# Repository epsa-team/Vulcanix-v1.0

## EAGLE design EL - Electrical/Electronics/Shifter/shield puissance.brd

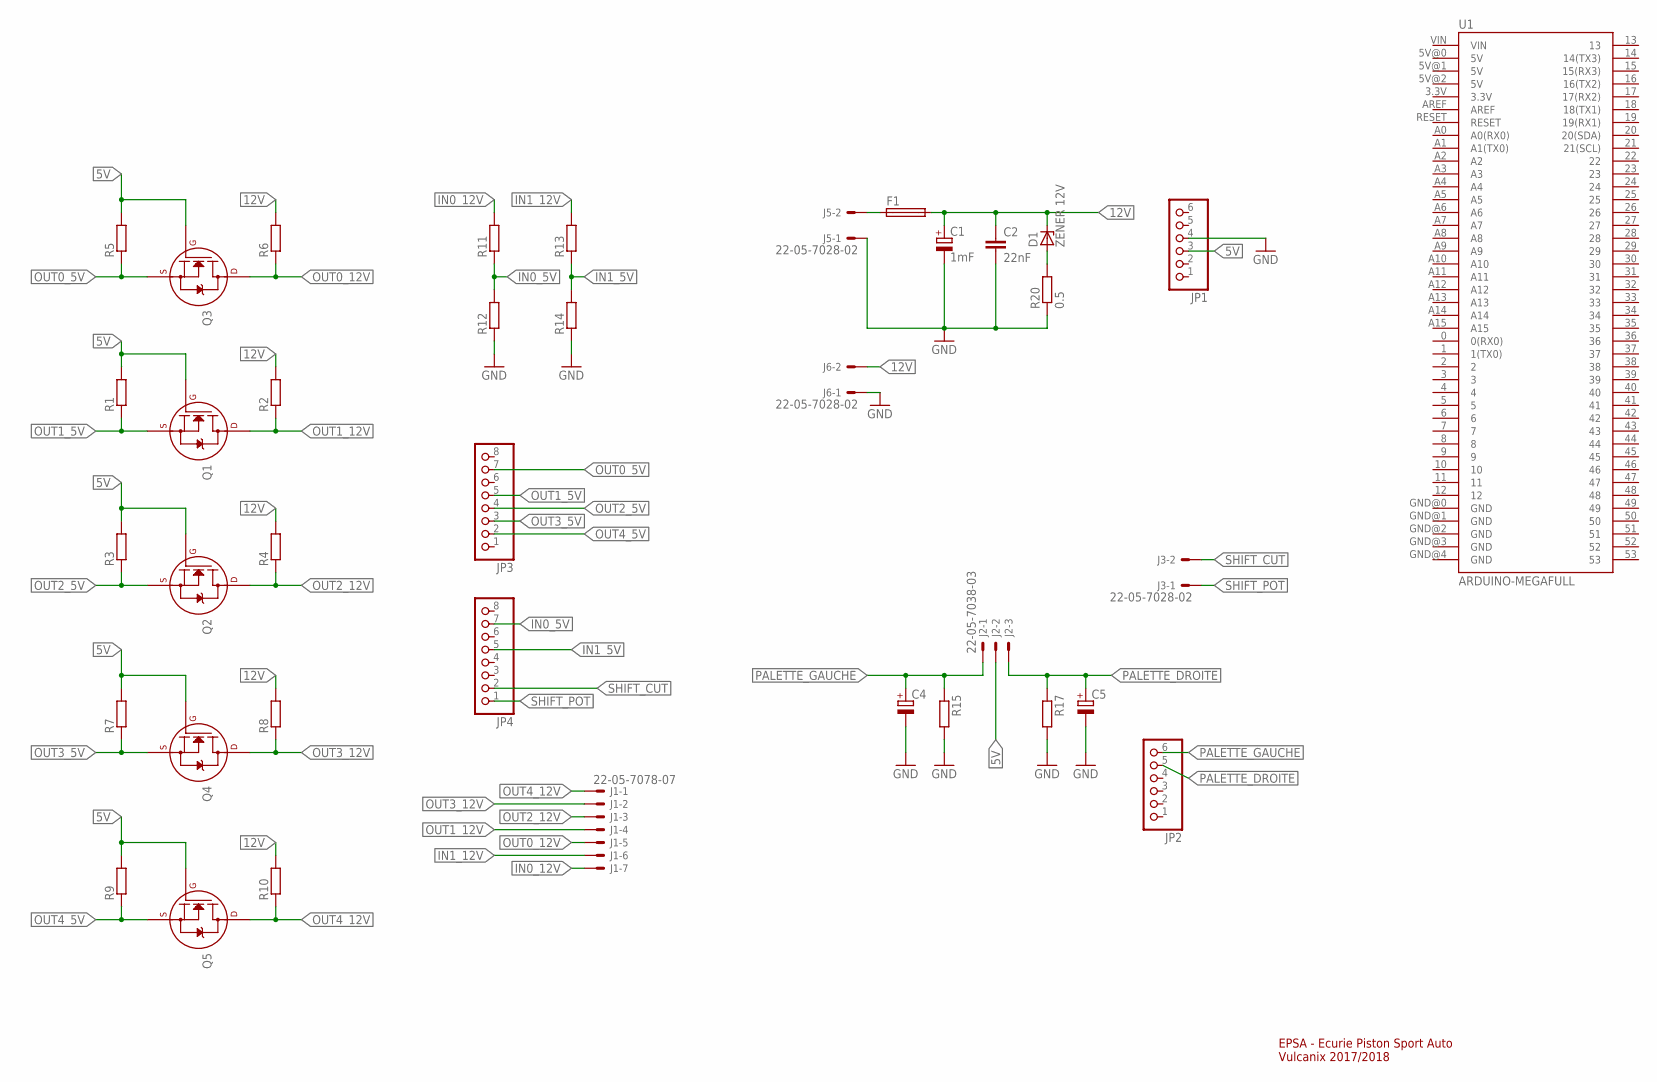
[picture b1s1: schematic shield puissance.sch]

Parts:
C1: 1mF; E2,5-6E
C2: 22nF; C025-025X050
C4, C5: CPOL-EUE2,5-6E; E2,5-6E
D1: ZENER 12V; DO41Z10
F1: SH25
J1: 22-05-7078-07; 7395-07
J2: 22-05-7038-03; 7395-03
J3, J5, J6: 22-05-7028-02; 7395-02
JP1, JP2: HEADER-1X6; 1X06_OVAL
JP3, JP4: HEADER-1X8; 1X08_OVAL
Q1, Q2, Q3, Q4, Q5: 2N7000_TO92; TO-92
R1, R2, R3, R4, R5, R6, R7, R8, R9, R10, R11, R12, R13, R14, R15, R17: R-EU_0204/7; 0204/7
R20: 0.5; 0309/12
U1: ARDUINO-MEGAFULL; ARDUINO_MEGA

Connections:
5V: J2.2, JP1.3, Q1.2 (G), Q2.2 (G), Q3.2 (G), Q4.2 (G), Q5.2 (G), R1.2, R3.2, R5.2, R7.2, R9.2
12V: C1.+, C2.1, D1.C, F1.2, J6.2, R2.2, R4.2, R6.2, R8.2, R10.2
GND: C1.-, C2.2, C4.-, C5.-, J5.1, J6.1, JP1.4, R12.1, R14.1, R15.2, R17.2, R20.1
IN0_5V: JP4.7, R11.1, R12.2
IN0_12V: J1.7, R11.2
IN1_5V: JP4.5, R13.1, R14.2
IN1_12V: J1.6, R13.2
unnamed: F1.1, J5.2
unnamed: D1.A, R20.2
OUT0_5V: JP3.7, Q3.1 (S), R5.1
OUT0_12V: J1.5, Q3.3 (D), R6.1
OUT1_5V: JP3.5, Q1.1 (S), R1.1
OUT1_12V: J1.4, Q1.3 (D), R2.1
OUT2_5V: JP3.4, Q2.1 (S), R3.1
OUT2_12V: J1.3, Q2.3 (D), R4.1
OUT3_5V: JP3.3, Q4.1 (S), R7.1
OUT3_12V: J1.2, Q4.3 (D), R8.1
OUT4_5V: JP3.2, Q5.1 (S), R9.1
OUT4_12V: J1.1, Q5.3 (D), R10.1
PALETTE_DROITE: C5.+, J2.3, JP2.5, R17.1
PALETTE_GAUCHE: C4.+, J2.1, JP2.6, R15.1
SHIFT_CUT: J3.2, JP4.2
SHIFT_POT: J3.1, JP4.1

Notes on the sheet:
EPSA - Ecurie Piston Sport Auto Vulcanix 2017/2018

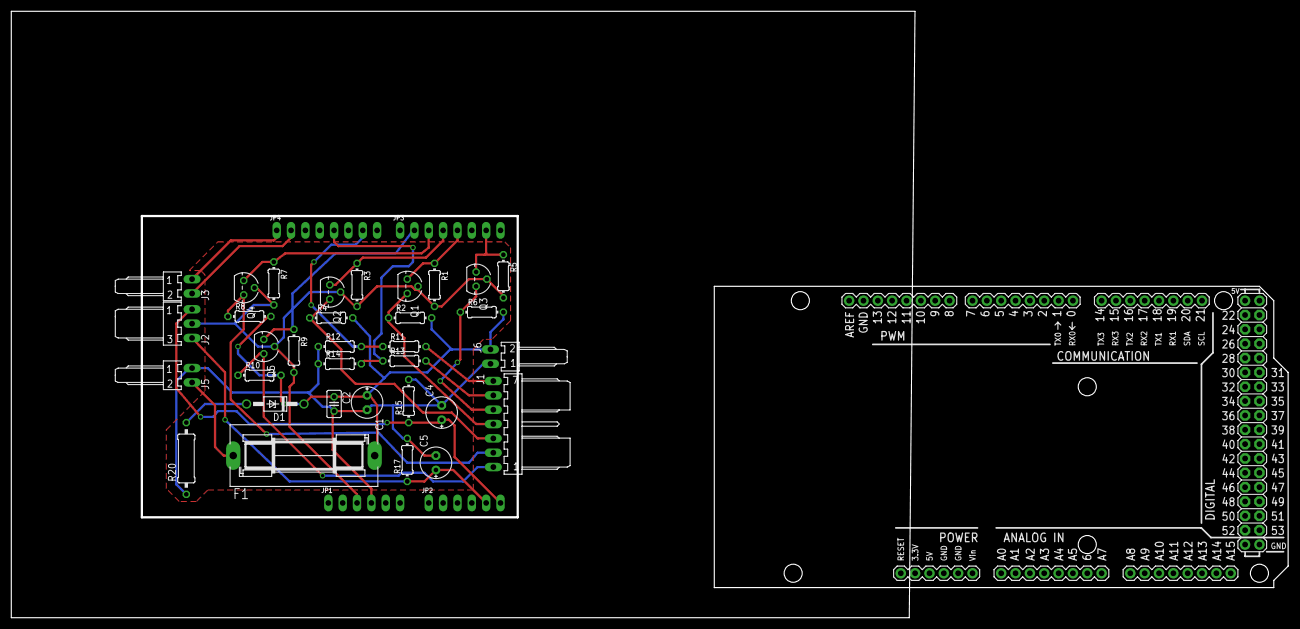
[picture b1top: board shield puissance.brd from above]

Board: 2 copper layers, 226.1 x 107.4 mm, 38 parts (0 on the bottom side), 23 nets.

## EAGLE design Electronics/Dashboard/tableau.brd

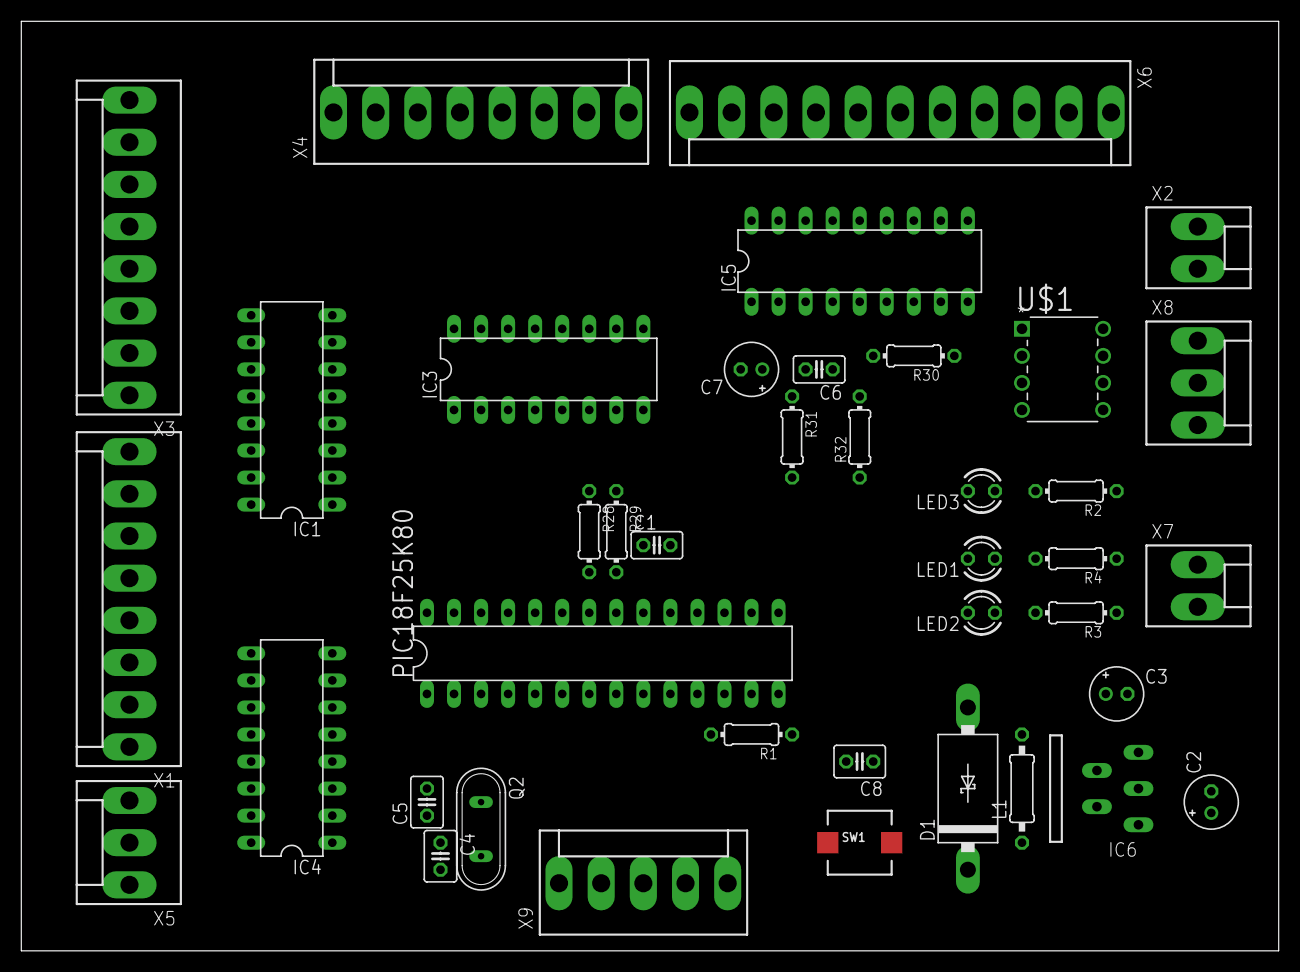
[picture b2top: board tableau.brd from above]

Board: 2 copper layers, 118.1 x 87.3 mm, 40 parts (0 on the bottom side), 69 nets, no tracks yet.

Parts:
C1: 0.1uF,20V; C025-025X050
C2, C3: 100uF; E2-5
C4, C5, C8: C025-030X050
C6: C025-025X050
C7: 10uF; E2-5
D1: 1N5822; DO201T15
IC1, IC3, IC4: 74LS47N; DIL16
IC5: LM3914N; DIL18
IC6: LM2576T; TO220-5
L1: 100uH; 0207/10
LED1, LED2, LED3: VERT; LED3MM
PIC18F25K80: PIC18F2580-I/SP; DIL28-3
Q2: QS
R1, R2, R3, R4, R28, R29, R30: 0204/7
R31: 3.83k; 0204/7
R32: 1.21k; 0204/7
SW1: PUSHBUTTON_SMD_SJ
U$1: MCP2551-I/P; DIP254P762X432-8
X1, X3, X4: KK-156-8
X2, X7: KK-156-2
X5, X8: KK-156-3
X6: KK-156-11
X9: KK-156-5

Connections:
CAN_H: U$1.6, X8.1
CAN_L: U$1.7, X8.3
CAN_RX: PIC18F25K80.24, U$1.4
CAN_TX: PIC18F25K80.23, U$1.1
D0EAU_0: IC4.7, PIC18F25K80.15
D0EAU_1: IC4.1, PIC18F25K80.16
D0EAU_2: IC4.2, PIC18F25K80.25
D0EAU_3: IC4.6, PIC18F25K80.26
D1EAU_0: IC1.7, PIC18F25K80.12
D1EAU_1: IC1.1, PIC18F25K80.11
D1EAU_2: IC1.2, PIC18F25K80.7
D1EAU_3: IC1.6, PIC18F25K80.6
D2EAU: PIC18F25K80.14, X5.1, X5.2
DRAP_0: IC3.7, PIC18F25K80.4
DRAP_1: IC3.1, PIC18F25K80.3
DRAP_2: IC3.2, PIC18F25K80.2
GND: C1.2, C2.-, C3.-, C4.1, C5.1, C6.2, C7.-, C8.1, D1.A, IC1.8, IC3.6, IC3.8, IC4.8, IC5.2, IC5.4, IC6.3, IC6.5, LED1.K, LED2.K, LED3.K, PIC18F25K80.8, PIC18F25K80.19, R28.1, R29.1, R31.1, SW1.P$1, U$1.2, U$1.8, X7.2, X8.2, X9.3
HOMING: PIC18F25K80.22, R28.2
MCLR: C8.2, PIC18F25K80.1, R1.1, SW1.P$2, X9.5
unnamed: LED1.A, R4.2
unnamed: IC4.13, X1.1
unnamed: LED2.A, R3.2
unnamed: IC4.12, X1.2
unnamed: IC4.11, X1.3
unnamed: IC4.10, X1.4
unnamed: IC4.9, X1.5
unnamed: IC4.15, X1.6
unnamed: IC4.14, X1.7
unnamed: IC1.13, X3.1
unnamed: IC1.12, X3.2
unnamed: IC1.11, X3.3
unnamed: IC1.10, X3.4
unnamed: IC1.9, X3.5
unnamed: IC1.15, X3.6
unnamed: IC1.14, X3.7
unnamed: IC3.13, X4.1
unnamed: IC3.12, X4.2
unnamed: IC3.11, X4.3
unnamed: C2.+, IC6.1
unnamed: IC3.10, X4.4
unnamed: IC3.9, X4.5
unnamed: IC3.15, X4.6
unnamed: IC3.14, X4.7
unnamed: IC5.10, X6.1
unnamed: IC5.11, X6.2
unnamed: IC5.12, X6.3
unnamed: IC5.13, X6.4
unnamed: IC5.14, X6.5
unnamed: IC5.15, X6.6
unnamed: IC5.16, X6.7
unnamed: IC5.17, X6.8
unnamed: IC5.18, X6.9
unnamed: IC5.1, X6.10
unnamed: LED3.A, R2.2
unnamed: C6.1, IC5.5, R30.2
unnamed: IC5.6, IC5.7, R32.2
unnamed: IC5.8, R31.2, R32.1
unnamed: D1.C, IC6.2, L1.1
NEUTRE: PIC18F25K80.21, R29.2
OSC1: C4.2, PIC18F25K80.9, Q2.2
OSC2: C5.2, PIC18F25K80.10, Q2.1
PGC: PIC18F25K80.27, X9.1
PGD: PIC18F25K80.28, X9.2
PWM_SHIFT: PIC18F25K80.13, R30.1
TESTLED_0: PIC18F25K80.5, R2.1
UART_RX: PIC18F25K80.18, X2.2
UART_TX: PIC18F25K80.17, X2.1
VBATTERY: R4.1, X7.1
VCC: C1.1, C3.+, C7.+, IC1.3, IC1.4, IC1.5, IC1.16, IC3.3, IC3.4, IC3.5, IC3.16, IC4.3, IC4.4, IC4.5, IC4.16, IC5.3, IC5.9, IC6.4, L1.2, PIC18F25K80.20, R1.2, R3.1, U$1.3, X1.8, X3.8, X4.8, X5.3, X6.11, X9.4

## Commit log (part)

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2018-03-03 correction de mes erreurs
2018-03-05 Placement du Master Switch
2018-03-05 repliage pare feu
2018-03-05 Placement de la nouvelle master switch
2018-03-05 update des igs
    voila on teste le githud desktop
2018-03-05 Rereplacement du master switch
2018-03-05 Gabarit de LAS.
2018-03-06 chapes Reservoir
    MEP e igs
2018-03-06 MeP fond plat
2018-03-06 Tube réservoir
2018-03-06 chapes divers
    mep igs et la mere de naldo
2018-03-06 chapes
    igs plan, cash cremailliere
2018-03-06 plan reservoir
2018-03-07 Las_auto
2018-03-07 Las auto elle plie tout
2018-03-07 VBA la pls
2018-03-07 Walah j'ai chibré
2018-03-07 Le VBA c'est la PLS
2018-03-07 Ajout Carter dhuile
    Ajout Carter d'huile
2018-03-07 MEP - Tank a gas
2018-03-07 mise en plan
2018-03-07 Vulcanix Finale Carter
    Mise a jour carter
2018-03-07 deplacement
2018-03-07 MEP insert PM arrière bas
2018-03-07 affichage commande
2018-03-07 Gabarits de ses morts
2018-03-07 preparation commande
2018-03-07 plans alu à souder cooling
2018-03-08 push-push-push
2018-03-08 Début mep insert pm lower front
2018-03-08 MIP gabarits de LAS
2018-03-08 Mate ça Lahm
2018-03-08 Ahah tu t'arrètes jamais !
2018-03-08 Modif-echappement
2018-03-09 Correction erreur Su Assy
2018-03-09 Bah attend, je suis pas la pour niaiser
2018-03-09 C'est quand même la PLS VBCatia
2018-03-10 Mep insert PM avant inf + modif largeur insert
2018-03-10 Mep Inset PM avant haut
2018-03-10 Mep insert avant haut 2
2018-03-10 Cartouche + modif insert sup arr PM
2018-03-11 new inser
2018-03-11 new triangles avant sup
2018-03-11 dessin
2018-03-11 blublublu
2018-03-11 plans
2018-03-11 des trucs
2018-03-11 maj mep portes-exc
2018-03-11 correction d'erreur
2018-03-11 Suppresion mep
2018-03-11 Modifications Gabarits
2018-03-11 yolo
2018-03-11 pour arthur
2018-03-11 plen pour envoyer
2018-03-11 Fin mep...
2018-03-12 Départ Prod pushrod
2018-03-12 Départ Prod tube fixation moteur
2018-03-12 MeP entretoises
2018-03-12 Auto stash before merge of "master" and "origin/master"
2018-03-12 Départ Prod pour pédalier
2018-03-12 Modif insert rear up
2018-03-12 Envoi en prod
2018-03-12 Chapes sa mere
    c presque fini
2018-03-13 nomenclature kit de montage
2018-03-13 kjijn
2018-03-13 gabarit chapes
2018-03-14 Bails de Gabarits
2018-03-14 Rectifications support de master switch
2018-03-14 Amélioration gabarits
2018-03-15 bracekt basculeur avant
    brah
2018-03-15 MEP
    wesh
2018-03-18 Aux grands maux les grands remèdes
2018-03-18 Je me repens
2018-03-19 Wallah
2018-03-19 gabarit transmi sec
2018-03-19 Cost Report
2018-03-19 Almost done XAP
    voila quoi
2018-03-20 envoie chaine shield roulé
2018-03-20 ajustement position chapes sur maquette Powertrain
2018-03-20 Création de Powertrain_avec_gabarit_chapes_transmi_secondaire
2018-03-21 ajout trou pour les cartes élec
2018-03-21 test svg pour Bob
2018-03-21 gabarits en svg
2018-03-21 zefqsdfqsgfqrfger
2018-03-21 Gabarits de direction
2018-03-21 version illustrator des gabarits du diff
2018-03-23 envoie frette
2018-03-23 1.5mm
2018-03-25 I'm back bitches
2018-03-25 Gabarit de manchon de direction fini
2018-03-26 new plan la mache
2018-03-26 cost
2018-03-26 Révision contraintes Transmission secondaire
2018-03-26 gabarits chapes + révision position chapes
2018-03-26 rien
2018-03-26 Coucou les plans
2018-03-26 more gabarit (+jacking bar)
2018-03-26 Je suis le seul con à faire mon cost.. ?
2018-03-26 gabgabgabgabgabgabgabgabgabgabgabgabgabgabgabgabgabgabgabgabgabgabgabgabgabgabgabgabgabgabgabgabgabgabgabgabgabgabgabgabgabgabgabgabgabgabgabgabgabgabgabgabgabgabgabgabgabgabgabgabgabgabgabgabgabgabg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
2018-03-26 Modif cardan
2018-03-27 copie du cost dans SU_A0100
2018-03-27 Go cost assy 1
2018-03-27 gabarit en .ai
2018-03-27 gabary moteur
2018-03-27 Cost frame
2018-03-27 Cost pédalier
2018-03-27 COSTa concordia
2018-03-27 Plan prod
2018-03-27 COST DRIVETRAIN : 30%
2018-03-27 Une belle merde ce pédalier
2018-03-27 COST DRIVETRAIN : A0900 fini (33%)
2018-03-27 Cost de JLE
2018-03-27 Cost JLE
2018-03-27 gabarit moteur
2018-03-27 Cost fond plat : Très bon choix l'aluminium par rapport au carbone
2018-03-27 COST DRIVETRAIN : début A_1000 (Driveshaft ) --> Process tripod housing à revoir
2018-03-28 maj macro las auto
2018-03-28 Cost batterie
2018-03-28 COST DRIVETRAIN : 60% (revoir axles) + reste Chain set
2018-03-28 cost firewall
2018-03-28 costi
2018-03-29 Plans utilisés pour l'usinage pour la postérité
2018-03-29 Comment je visite les tréfonds de CATIA avec ce projet ...
2018-03-29 Cost carrosserie
2018-03-31 COST DRIVETRAIN : on y croit !
2018-03-31 chai pas
2018-03-31 Vérif longueur axes
2018-03-31 MEP arbres finale
2018-03-31 COST DRIVETRAIN : Differential Assy + Driveshaft Assy terminés (reste Chain Set)
2018-04-01 COST DRIVETRAIN : 100%
2018-04-02 Wallah symmétrie
2018-04-02 COST DRIVETRAIN : correction remarques CME
2018-04-03 N truc de chapes mais normalement c les derniers
    LALALALA
2018-04-03 Gabarit chapes basculeur arrière
2018-04-08 Mep exhaust
2018-04-12 Maj PLM
2018-04-12 Again
2018-04-12 C'est ok lahm normalement
2018-04-12 Déchibrage de l'espace temps
2018-04-12 Wallah c'était galère
2018-04-13 easy le CIR
2018-04-15 J'adore le cost
2018-04-15 plop
2018-04-16 Maj cost frame
2018-04-18 nouveau harnais
2018-04-18 je sais pas
2018-04-21 Début cost ST
2018-04-23 je sais ap
2018-04-24 gabarit tdb
2018-04-24 Rapport wallah
2018-04-24 yolo strat
2018-04-25 Yo mznnn
    Yo
2018-04-25 Cost JLE 2
2018-04-25 Cost RMT
2018-04-25 Cost MS au complet [ne pas modifier !!]
2018-04-26 Le cost avance
2018-04-26 Cost ESR admission + throttle
2018-04-26 Voilà
2018-04-26 Cost echappement v2
2018-04-26 COST EN (pas terminé - ne pas modifier)
2018-04-28 Cost suspensions
2018-04-29 Cost MS corrigé par CME et PAT
2018-04-29 cost again
2018-04-29 Cost JLE corrigé par RMT
2018-04-29 Cost EN modifié (c'est pour toi Emilien ;) )
2018-04-29 ajout du tdb
2018-04-29 La fin approche !
2018-04-29 encore du cost
2018-04-30 Il m'entraine...au bout de la nuit....le...cost de minuit !
2018-04-30 Gabarits arbres de transmission
2018-04-30 Cost report EN_A001 and EN_A005
    Cost report engine (not finished) and fuel tank (finished)
2018-04-30 blebleble
2018-04-30 modif t eau
2018-04-30 Cost Engine
    Modifs cost
2018-04-30 Presque fini... Juste couleurs à changer
    Reste couleur à changer
2018-04-30 Fin cost EN_A001, EN_A005 et EN_A006
    Modif couleurs pour coller au template
2018-04-30 Cost catch can
    Omg
2018-04-30 Cost direction fini à 2 pièces près
2018-04-30 Ajout Palettes cost
2018-04-30 Cost cost cost
2018-05-01 Merci pour ce moment <3 (Cost des suspensions fini)
2018-05-01 cost cooling
2018-05-01 MAJ finale Cost Admission
2018-05-01 Cost Julien sur SU
2018-05-01 Cost JLE corrigé VERSION v2
2018-05-01 Cost FR
2018-05-02 Cost_FR_global_cor_RMT
2018-05-02 Le cost avance un peu...
2018-05-02 Cost FR avec images (cor RMT)
2018-05-02 Avec plans inserts. Reedom : images déjà compressé
2018-05-02 Ajout des images de Benji
2018-05-02 Cost moyeu avant et roue
2018-05-02 Cost WT [pas terminé] → il manque WT_A0300 !
2018-05-03 Ajout EN_A0100→reste à ajouter EN_A0500 à EN_A0800
2018-05-03 Jtravaille sur cost SU donc n'allez pas dessus
    Cost mamene
2018-05-03 COST Su de mes couilles
2018-05-03 Cost SU
2018-05-03 Cost_SU...
    Merci Lazure pour le travail
2018-05-03 Cost FR totalement terminé
2018-05-03 Modif cache crémaillère
2018-05-03 Cost FR terminé- external et internal spacer suppr
2018-05-03 Finalisation cost
2018-05-03 Cost BR Pierre
2018-05-03 Cost BR cor RMT
2018-05-03 Cost EL_A0100
2018-05-03 Steering_correction_CME
2018-05-03 Cost EL_A0300
2018-05-03 Merci CME
2018-05-03 Cost EN fini cor RMT
2018-05-03 Costcost
2018-05-03 BOM Steering Complet
2018-05-03 Encore du boulot...
2018-05-04 costocosto
2018-05-04 Cost SU pas terminé
2018-05-04 Fin cost triangles
2018-05-04 Cost SU jusqu'à 7
2018-05-04 Cost_SU jusquà assy 9
2018-05-04 Mise en forme BOM
2018-05-04 Tranquille
2018-05-04 Fin cost SU
2018-05-04 Push push
2018-05-04 Début assemblage final
2018-05-04 Cost BR complètement fini (cor CME et liens ok)
2018-05-04 Cost EN fini (cor CME + qtité process 2 EN81 cor)
2018-05-04 Su + steering (en cours)
2018-05-04 Cost steering terminé
2018-05-04 Assemblage break + travail wheels
2018-05-04 Cost global + wheel
2018-05-04 Cost SU / PM ok pour moi
2018-05-04 Cost EL fini - cor RMT
2018-05-04 Cost steering final avec liens refaits (RMT)
2018-05-04 Push WT
2018-05-04 Cost WT fini - cor RMT et ABR
2018-05-04 Cost SU cor RMT et ABR
2018-05-04 Correction
2018-05-04 Cost global v2
2018-05-04 Cost global v3 (avec num de pages)
2018-05-04 Cost Vulcanix v4 -avec num de ligne et cor couleur
2018-05-04 Ciao le cost
2018-05-04 BOM officiellement envoyée à la compèt
2018-05-06 Bru ?
2018-05-08 Le retour de la LAS auto
2018-05-08 Pour backup acier
2018-05-12 Mise à jour arbres de transmission. Plans et maquette CATIA
2018-05-16 viuiuh
2018-05-17 Merge
2018-05-21 New Side Firewall
2018-05-21 Firewall V2
2018-05-23 Pare feu V2
2018-05-24 no message
2018-05-24 Paaaaaaaaaare feu
2018-05-24 Pare feu sa mere
2018-05-24 Fiches Essais
2018-05-28 Firewall MeP
2018-05-28 Ajout fiche pilote
2018-05-28 Cache crémaillère grand
2018-05-28 sauvegarde agressive
2018-05-28 Retour tube avant
2018-05-28 Cache crémaillère 2
2018-05-28 Qui ose sacager le GIT ?
2018-05-29 découpe tdb
2018-05-29 Resolution probleme double fond plat
2018-05-29 Résolution probleme carrosserie double
2018-05-29 recallage arbres pour les vues
2018-05-29 Pare feu raccord tube
2018-05-29 Ok position chapes chainshield sur Vulcanix
2018-05-29 firewall tube
2018-05-29 Pushbar update
2018-05-29 maj sleeve joint
2018-05-29 maj chape harnais
2018-05-29 replacement des led du tdb
2018-05-30 maj chassis
2018-05-30 renoie prod pare fue
2018-05-30 Pushbar v3.0
2018-05-31 MeP Firewall
2018-06-01 placement boitier avant.
2018-06-02 Préparation maquette design
2018-06-03 Les repères jaunes ça dégage et la direction est presque droite
2018-06-03 idem
2018-06-06 italian design touch
2018-06-06 italian design push
2018-06-07 design
2018-06-08 plans pushbar
2018-06-13 pour l'iad
2018-06-13 mise en plan caches crémaillères
2018-06-13 plan pushbar
2018-06-23 ca passe ?
2018-06-23 Elle est enfin la !
2018-06-23 lourd
2018-06-24 Voila enfin les courbes
2018-06-25 azerty
2018-06-25 correction des erreurs
2018-06-26 arduino dans boite avant
2018-07-01 update figure
2018-07-06 Upload dossier design
2018-08-13 ?
    ?
2018-08-13 Real case
2018-08-14 Ajout courbes test traction
2018-08-15 Check list voiture essais
2018-08-21 Test cinématiques ARB pour Optimus
2018-11-12 pedal
2018-12-16 le retour de vulcanix

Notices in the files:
parts and their libraries:
microbuilder: This work is placed in the public domain, and may be freely used for commercial and non-commercial work with the following conditions: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
SparkFun-Boards: Licensing: CC v3.0 Share-Alike You are welcome to use this library for commercial purposes.
